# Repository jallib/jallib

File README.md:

# Welcome to **Jallib** 

This project holds a set of JAL libraries, compatible with the **JALV2** compiler. 
JAL is a high-level language for the Microchip 8-bits PIC microcontrollers of the
Baseline, Midrange, Enhanced Midrange and 18F series.

Lots of libraries exist, built by authors all over the world. The aim of this project is to:
 * Centralize these libraries.
 * Propose standards to write and share JAL code.

This avoids re-inventing the wheel and helps sharing code.

If you're looking for a specific library, welcome here! You may want to:
 * [Download](http://www.justanotherlanguage.org/downloads) one of our packages.
 * Browse our repository and retrieve sources. 
 * Browse the [Jal users site](http://www.justanotherlanguage.org) for introductions to JAL
in general and the use of several Jallib libraries in particular.

For a quick start on how to install Jallib, compile and run a jal program on your PIC have a look at [Installing and using Jallib](https://github.com/jallib/jallib/wiki/Installing-and-using-Jallib).

Also have a look at **UnixCompilingFromSvnHowto** wiki. It'll help you to use the whole repository.
 * jalapi is the jallib API documentation
 * have a look at our [jallib discussion group](https://groups.google.com/forum/#!forum/jallib),
where you can get some help on jallib libraries, jallib development or
* have a look at our [jallist discussion group](https://groups.google.com/forum/#!forum/jallist) where you can discuss coding issues with jal and PIC

The repository is organized in such a way that it is easy to find where you are looking for
(libraries, sample programs, device files, etc...). 
For a complete description, see the [Understanding The GitHub Structure](https://github.com/jallib/jallib/wiki/Understanding-The-GitHub-Structure) wiki.

If you plan to contribute, if you dare to put your head over the mowing field, welcome again! 
Go to the jallib discussion group and request to join us. 
For write access to the repository you'll need **GitHub account**. 
We'll be glad to send you a membership invitation! 
Once registered, you should have a look at our **JallibStyleGuide**. 
It will explain know some basic principles, rules, etc... 
which everyone must obey to provide efficient, understandable code. 
As a member, have a look at our [Jallib File Structure](https://github.com/jallib/jallib/wiki/Jallib-File-Structure). 
You'll be able to access our repository as an official committer!

Have fun !

The **Jallib team**.

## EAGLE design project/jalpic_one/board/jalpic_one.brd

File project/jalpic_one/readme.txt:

Information on the JALPIC One development board
===============================================

source
-------
Contains all source files of the controller PIC software
The Hex file for the controller PIC is also included in this directory.

examples
---------
Contains the two examples for showing the operation of the application PIC.
These examples are used in the documentation. This directory also contains
the jalpic_one.jal include file which has to be included by every program
that needs to run on the application PIC.
The Hex files of both example programs are also included in this directory.

board
-----
Contains all files used to create the board. These are:
-) Schematic diagram designed in Eagle 9.31
-) Board design designed in Eagle 9.31
-) PDF of the schematic diagram
-) PDF of the board design
-) PDF of the component layout
-) Screenshot of the board layout
-) Zipfile containing the Gerber files. This zipfile is used by the pcb
   manufacturer to manufacture the board.

doc
---
MS Word file of the user manual of the JALPIC One development board
PDF of the user manual of the JALPIC One development board

Tools
-----
This contains a zip file with 3 parts:
1) File jalpic_one.py. Python script to easy the programming of the JALPIC One development board.
2) Compiled version of jalpic_one.py for Windows 32-bit.
3) Compiled version of jalpic_one.py for Windows 64-bit.
See the manual on how to create a compiled version of this script.
When using the compiled version, Python does not have to be installed.

Notes
-----
After the zip file with the Gerber file was created, some small additions were made in the
silk screen of the board desing, e.g adding the text 'JALPIC One'. The board design itself
was not changed but note that when the zipfile is used to order a board, this text will not
be on it unless a new zipfile with Gerber file is created.

When using Python you need to have PySerial installed:
-) Python website: https://www.python.org/
-) Install PySerial: python -m pip install pyserial

A short video on how the board works can be found on: https://www.youtube.com/watch?v=lj-_5-6WYTY

Rob Jansen
2019-04-05

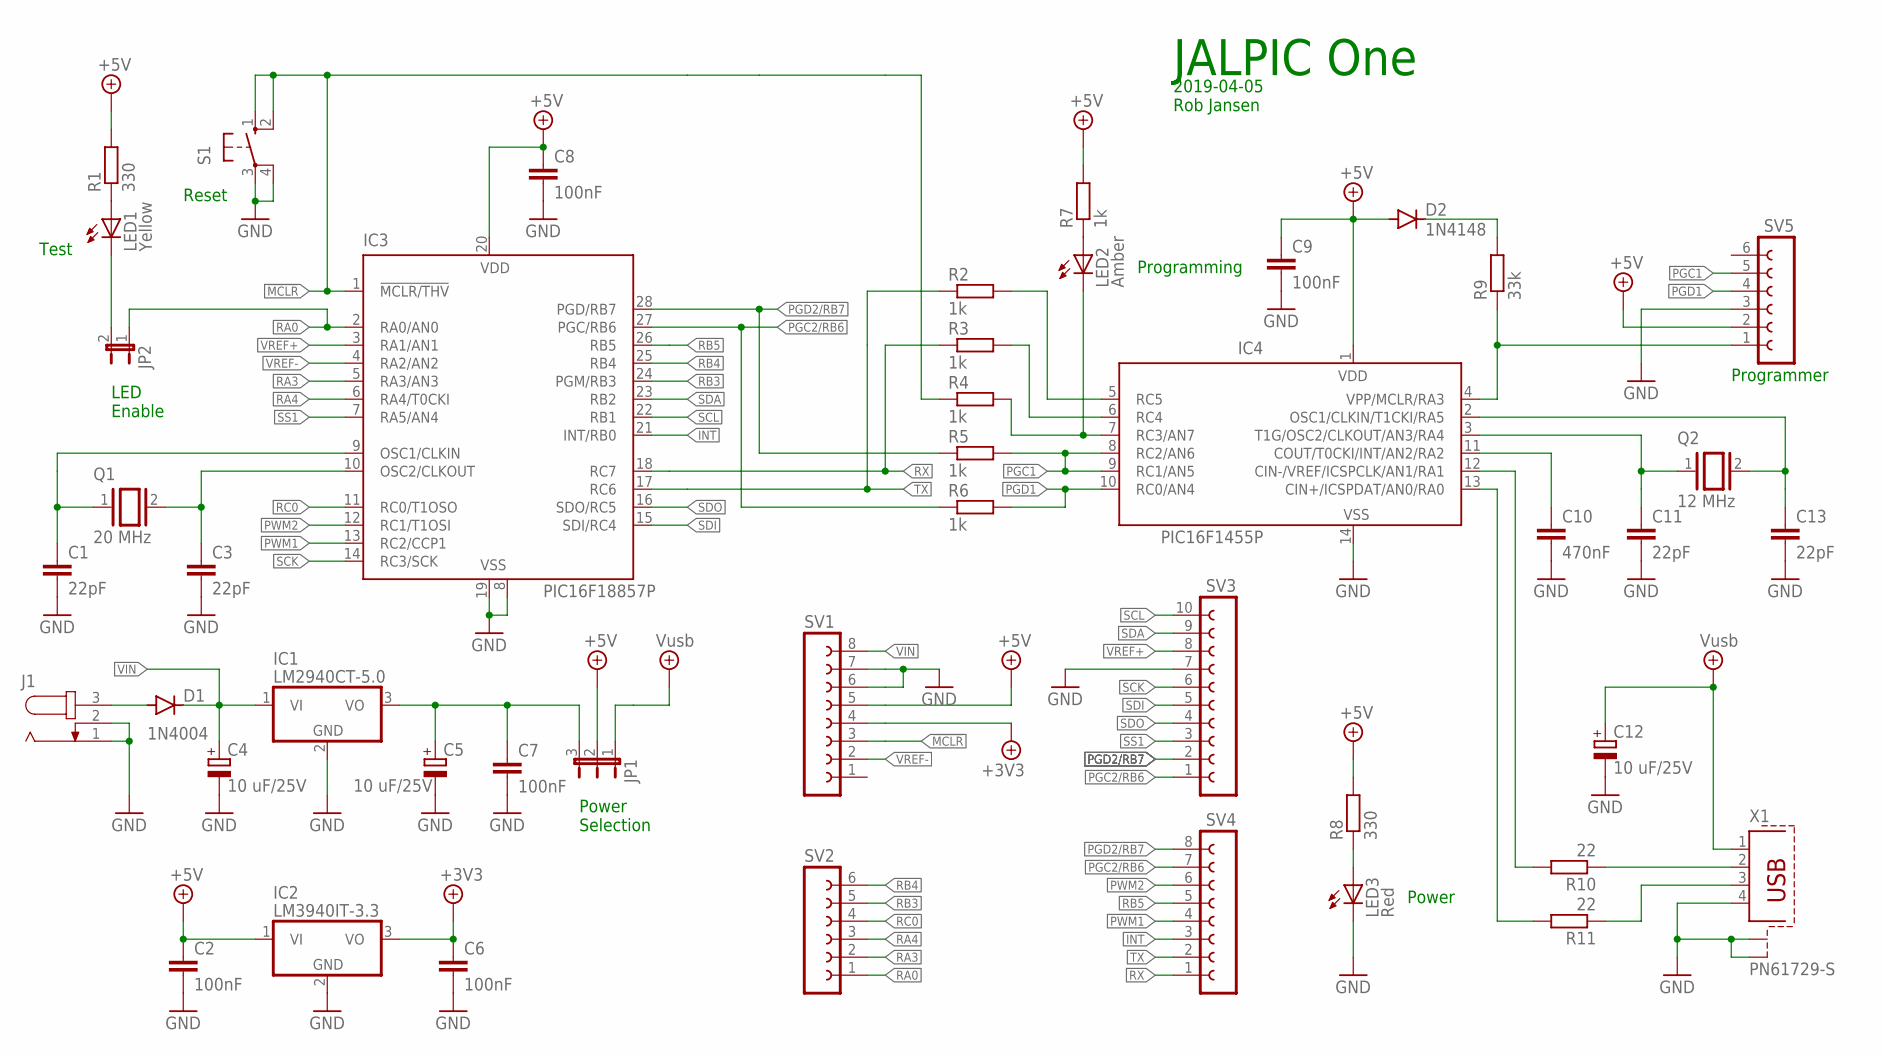
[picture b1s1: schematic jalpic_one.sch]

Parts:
C1, C3, C11, C13: 22pF; C050-024X044
C2, C6, C7, C8, C9: 100nF; C050-024X044
C4, C5, C12: 10 uF/25V; E2-5
C10: 470nF; C050-024X044
D1: 1N4004; DO35-7
D2: 1N4148; DO35-7
IC1: LM2940CT-5.0; TO220V
IC2: LM3940IT-3.3; TO220V
IC3: PIC16F18857P; DIL28-3
IC4: PIC16F1455P; DIL14
J1: JACK-PLUG0; SPC4077
JP1: JP2E; JP2
JP2: JP1E; JP1
LED1: Yellow; LED5MM
LED2: Amber; LED5MM
LED3: Red; LED5MM
Q1: 20 MHz; QS
Q2: 12 MHz; QS
R1, R8: 330; 0207/7
R2, R3, R4, R5, R6, R7: 1k; 0207/7
R9: 33k; 0207/7
R10, R11: 22; 0207/7
S1: 10-XX; B3F-10XX
SV1, SV4: FE08-1; FE08
SV2, SV5: FE06-1; FE06
SV3: FE10-1; FE10
X1: PN61729-S

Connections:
!MCLR: IC3.1 (!MCLR/THV), R4.1, S1.1 (S), S1.2 (S1), SV1.3
+4.1V: C6.1, IC2.3 (VO), SV1.4
+5V: C2.1, C8.1, C9.1, D2.A, IC2.1 (VI), IC3.20 (VDD), IC4.1 (VDD), JP1.2, R1.2, R7.2, R8.2, SV1.5, SV5.2
+9V: C12.+, JP1.1, X1.1
GND: C1.2, C2.2, C3.2, C4.-, C5.-, C6.2, C7.2, C8.2, C9.2, C10.2, C11.2, C12.-, C13.2, IC1.2 (GND), IC2.2 (GND), IC3.8 (VSS), IC3.19 (VSS), IC4.14 (VSS), J1.1, J1.2, LED3.K (C), S1.3, S1.4 (P1), SV1.6, SV1.7, SV3.7, SV5.3, X1.4, X1.S1, X1.S2
INT: IC3.21 (INT/RB0), SV4.3
unnamed: D1.A, J1.3
unnamed: IC4.4 (VPP/MCLR/RA3), R9.1, SV5.1
unnamed: JP2.2, LED1.K (C)
unnamed: C5.+, C7.1, IC1.3 (VO), JP1.3
unnamed: C10.1, IC4.11 (COUT/T0CKI/INT/AN2/RA2)
unnamed: LED1.A, R1.1
unnamed: LED3.A, R8.1
unnamed: IC4.7 (RC3/AN7), LED2.K (C), R4.2
unnamed: IC4.12 (CIN-/VREF/ICSPCLK/AN1/RA1), R10.2
unnamed: C11.1, IC4.3 (T1G/OSC2/CLKOUT/AN3/RA4), Q2.1
unnamed: C13.1, IC4.2 (OSC1/CLKIN/T1CKI/RA5), Q2.2
unnamed: C3.1, IC3.10 (OSC2/CLKOUT), Q1.2
unnamed: IC4.6 (RC4), R3.2
unnamed: IC4.5 (RC5), R2.2
unnamed: IC4.13 (CIN+/ICSPDAT/AN0/RA0), R11.2
unnamed: C1.1, IC3.9 (OSC1/CLKIN), Q1.1
unnamed: LED2.A, R7.1
unnamed: R10.1, X1.2
unnamed: R11.1, X1.3
unnamed: D2.C, R9.2
PGC1: IC4.8 (RC2/AN6), IC4.9 (RC1/AN5), R5.2, SV5.5
PGC2/RB6: IC3.27 (PGC/RB6), R6.1, SV3.1, SV4.7
PGD1: IC4.10 (RC0/AN4), R6.2, SV5.4
PGD2/RB7: IC3.28 (PGD/RB7), R5.1, SV3.2, SV4.8
PWM1: IC3.13 (RC2/CCP1), SV4.4
PWM2: IC3.12 (RC1/T1OSI), SV4.6
RA0: IC3.2 (RA0/AN0), JP2.1, SV2.1
RA3: IC3.5 (RA3/AN3), SV2.2
RA4: IC3.6 (RA4/T0CKI), SV2.3
RB3: IC3.24 (PGM/RB3), SV2.5
RB4: IC3.25 (RB4), SV2.6
RB5: IC3.26 (RB5), SV4.5
RC0: IC3.11 (RC0/T1OSO), SV2.4
RX: IC3.18 (RC7), R3.1, SV4.1
SCK: IC3.14 (RC3/SCK), SV3.6
SCL: IC3.22 (RB1), SV3.10
SDA: IC3.23 (RB2), SV3.9
SDI: IC3.15 (SDI/RC4), SV3.5
SDO: IC3.16 (SDO/RC5), SV3.4
SS1: IC3.7 (RA5/AN4), SV3.3
TX: IC3.17 (RC6), R2.1, SV4.2
VIN: C4.+, D1.C, IC1.1 (VI), SV1.8
VREF+: IC3.3 (RA1/AN1), SV3.8
VREF-: IC3.4 (RA2/AN2), SV1.2

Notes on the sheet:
JALPIC One
2019-04-05 Rob Jansen
Power
Power Selection
Programming
Reset
Programmer
LED Enable
Test

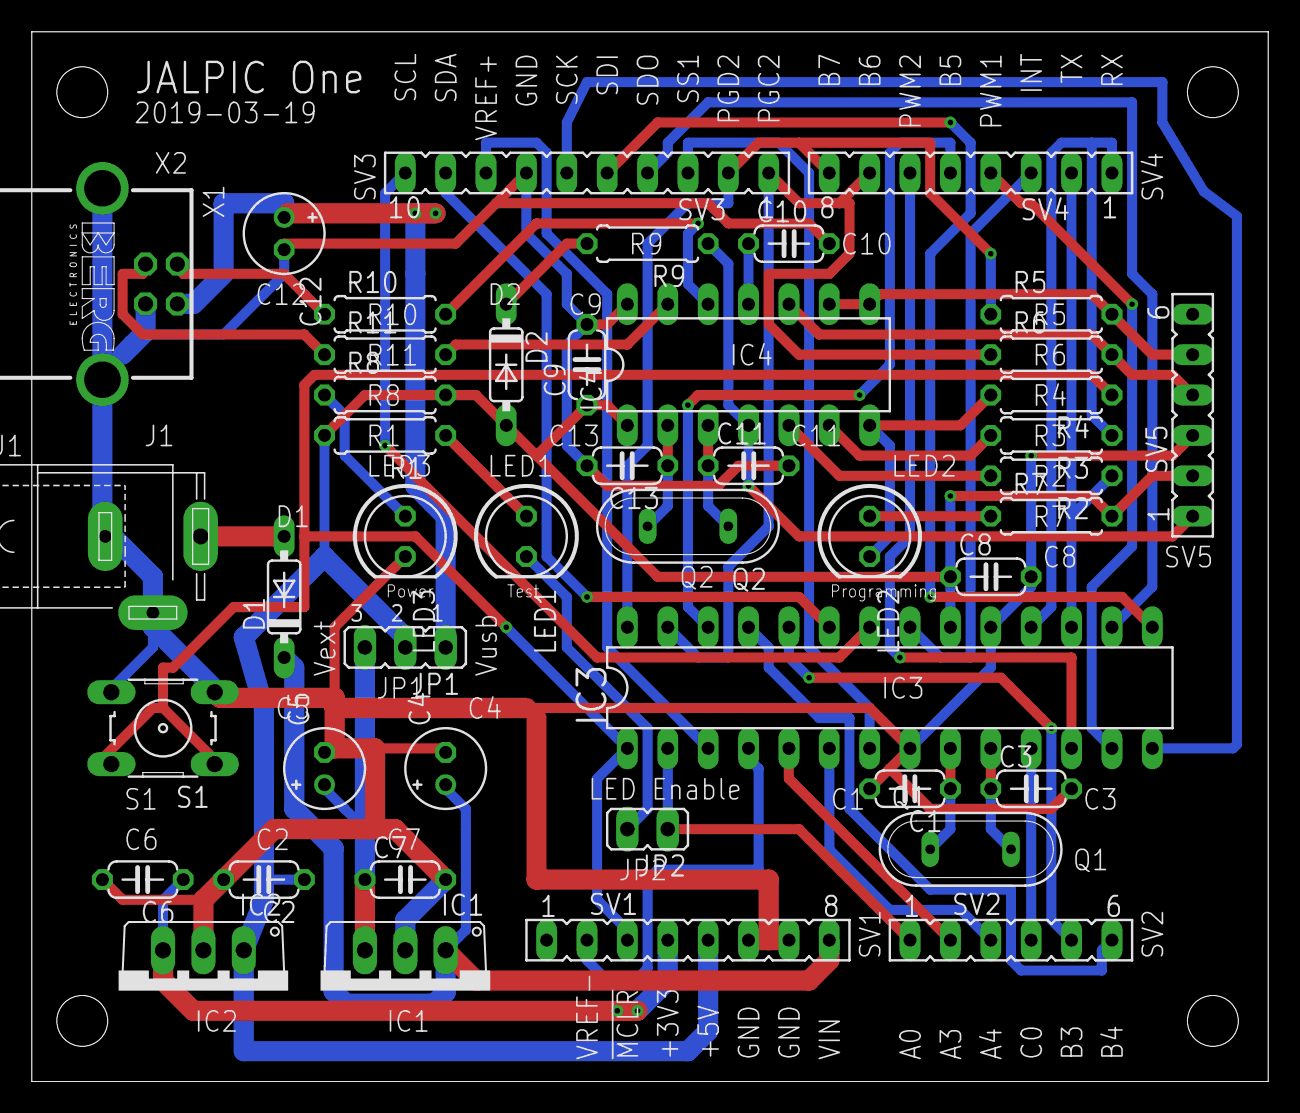
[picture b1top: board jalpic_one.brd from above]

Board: 2 copper layers, 77.8 x 66.0 mm, 45 parts (0 on the bottom side), 50 nets.

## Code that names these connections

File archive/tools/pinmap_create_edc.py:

#!/usr/bin/python

"""
   pinmap_create.py - create new pinmap.py from MPLAB-X
   This script is part of a sub-project using MPLAB-X info for Jallib,
   in particular the device files, but also for some other libraries.
   This script uses the .edc files created by the pic2edc script.
   The Pin section of these files contains the pin aliases.
   Some manipulations are performed, for example:
    - skip pins which are not accessible from the program like Vpp, Vdd
    - skip non-aliases of a pin, like IOC, INT
    - correct apparent errors or omissions of MPLAB-X
    - determine the base name of a pin and specify it as first in list
   When pins are not in .edc file or known to be incorrect
   the entry in the old pinmap file will be copied (when present).
   Same when the .edc file does not contain a Pin section at all,
   otherwise the pinmap will not contain an entry for this PIC and
   must be created manually from the datasheet.
   This script handles issues with MPLAB-X (version see below).
   for other MPLAB-X versions it will probably have to be adapted!
"""

import os
import sys
import fnmatch
import re
from xml.dom.minidom import parse, Node

mplabxversion = "205"                                       # latest version of MPLAB-X

edcdir    = "k:/jal/edc2jal/edc_" + mplabxversion           # dir with .edc files
pinmapnew = "pinmapnew.py"                                  # output

portpin = re.compile(r"^R[A-L]{1}[0-7]{1}\Z")               # Rx0..7 (x in range A..L)
gpiopin = re.compile(r"^GP[0-5]{1}\Z")                      # GP0..5

dir = fnmatch.filter(os.listdir(edcdir), "*.edc")           # get list of .edc files
if len(dir) == 0:
   print "No .edc files found in directory", edcdir
   sys.exit(1)

print "Building new pinmap from .edc files in", edcdir, "for (max)", len(dir), "PICs"

try:
   fp = open(pinmapnew, "w")
except IOError:
   print "Could not create output file", pinmapnew
   sys.exit(1)


def list_pic(_pic, _alias):
# list all pins and their aliases of a single _pic in dictionary _alias
   header = '   "' + _pic + '": {'                          # start of pinmap this PIC
   fp.write(header)
   pinlist_sorted = list(_alias.keys())
   pinlist_sorted.sort()
   for i in range(len(pinlist_sorted) - 1):                 # all but last
      pin = pinlist_sorted[i]
      fp.write('"' + pin + '" : ["' + '", "'.join(_alias[pin]) + '"],\n' + " "*len(header))
   pin = pinlist_sorted[-1]
   fp.write('"' + pin + '" : ["' + '", "'.join(_alias[pin]) + '"]\n' + " "*len(header))
   fp.write("},\n")                                         # end of pinmap this PIC


from pinmap import pinmap                                   # current ('old') pinmap

dir.sort()                                                  # alphanumeric sequence
piccount = 0
fp.write("pinmap = {\n")                                  # pinmap header

for filename in dir:
   picname = os.path.splitext(filename)[0][0:].upper()      # determine PIC from filename
   print picname

   if (picname in ("16LF1713", "16F1716", "16LF1716")):
      filename = "16f1713.edc"
      print "  Pinmap derived from 16f1713"

   filepath = os.path.join(edcdir,filename)                 # pathspec
   dom = parse(filepath)                                    # load .edc file

   pinnumber = 0
   pinlist = {}                                             # new dictionary
   for pin in dom.getElementsByTagName("edc:Pin"):          # select pin nodes
      pinnumber = pinnumber + 1                             # calculated next pin, maybe
      for pinc in pin.childNodes:                           #   corrected by comment node
         if pinc.nodeType == pinc.COMMENT_NODE:
            wlist = pinc.nodeValue.split()
            if wlist[0].isdigit() == True:
               pinnumber = int(wlist[0])
            elif wlist[1].isdigit() == True:
               pinnumber = int(wlist[1])
      aliaslist = []                                        # new aliaslist this pin
      for vpin in pin.getElementsByTagName("edc:VirtualPin"):
         alias = vpin.getAttribute("edc:name").upper().strip("_")
         if alias not in ("INT", "IOC"):                    # only 'real' alias names
            if alias.startswith("RB")  & picname.startswith("12"):   # Jallib requirement
               aliaslist.append("RA" + alias[-1])           # RBx -> RAx
               aliaslist.append("GP" + alias[-1])           # add GPx
               print "  Renamed pin", alias, "to RA" + alias[-1]
            elif alias in("RB1AN10", "RC7AN9"):             # MPLAB-X errors
               aliaslist.append(alias[0:3])
               aliaslist.append(alias[3:])
               print "  Splitted alias", alias, "into", alias[0:3], "and", alias[3:], "for pin", pinnumber
            elif alias == "DAC1VREF+N":                     # MPLAB-X error
               aliaslist.append("DAC1VREF+")
               print "  Replaced", alias, "by DAC1VREF+ for pin", pinnumber
            elif alias == "NMCLR":
               aliaslist.append("MCLR")
               print "  Replaced", alias, "by MCLR for pin", pinnumber
            elif ( (picname in ("16F1707", "16LF1707")) &
                   (alias == "AN9") & (pinnumber == 8) ):
               aliaslist.append("AN8")
               print "  Replaced alias", alias, "by AN8 for pin", pinnumber
            elif ( (picname in ("18F2439", "18F2539", "18F4439", "18F4539")) &
                   (alias.startswith("PWM")) ):
               aliaslist.append(alias)
               if alias[-1] == "1":
                  aliaslist.append("RC2")                   # MPLAB-X omission
                  print "  Added RC2 to pin", pinnumber
               else:
                  aliaslist.append("RC1")
                  print "  Added RC1 to pin", pinnumber
            else:
               aliaslist.append(alias)                      # normal alias!

      if (picname in ("18F2331", "18F2431")) & (pinnumber == 26):
         aliaslist = ["RE3"] + aliaslist                    # prepend missing pin name
         print "  Added RE3 to pin", pinnumber
      elif (picname in ("18F4220", "18F4320")) & (pinnumber == 36):  # MPLAB-X omission
         aliaslist = pinmap[picname].get("RB3", ["RB3"])    # copy from old pinmap if present
         print "  Aliaslist of pin", pinnumber, "copied from old pinmap"
      elif (picname in ("18F86J11", "18F86J16", "18F87J11"))  & (pinnumber == 55):
         aliaslist = pinmap[picname].get("RB3", ["RB3"])    # copy from old pinmap if present
         print "  Aliaslist of pin", pinnumber, "copied from old pinmap"

      portbit = None
      for alias in aliaslist:
         if re.match(portpin,alias):                        # check for Rxy
            portbit = alias
            if portbit != aliaslist[0]:                     # not first in list
               aliaslist.remove(portbit)
               aliaslist = [portbit] + aliaslist            # shift to front
            break
         elif re.match(gpiopin,alias):                      # check gor GPx
            portbit = "RA" + alias[-1]                      # note: RAx not in aliaslist!
            break
      if portbit != None:                                   # found Rxy or GPx
         if portbit in pinlist:
            print "  Duplicate pin specification:", portbit, "pin", pinnumber, "skipped"
         else:
            pinlist[portbit] = aliaslist                    # add aliaslist this pin


   if picname in ("16F1704", "16LF1704"):
      for pin in ("RB4", "RB5", "RB6", "RB7", "RC6", "RC7"):
         if pinlist.get(pin) == None:                       # MPLAB-X omission
            if pinmap[picname].get(pin) != None:            # pin present in old pinmap
               pinlist[pin] = pinmap[picname].get(pin)      # take it from old pinmap
               print "  Copied missing alias list of pin", pin, "from old pinmap"
            else:
               pinlist[pin] = [pin]                         # insert dummy
               print "  Inserted dummy alias list for missing pin", pin

   if len(pinlist) > 0:
      list_pic(picname, pinlist)                            # list pinmap this pic
      piccount += 1
   elif pinmap.get(picname) != None:                        # present in old list
      list_pic(picname, pinmap[picname])                    # copy old mapping
      piccount += 1
      print "  Pinlist missing in .edc file, entry copied from current pinmap"
   else:
      print "  Pinlist missing, add it manually!"

fp.write("  }\n")                                           # end of pinmap
fp.close()

print "Generated pinmap", pinmapnew, "for", piccount, "PICs"
print "Compare new with current, when OK copy", pinmapnew, "to pinmap.py"

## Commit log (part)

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2021-01-03 Added new blink samples using internal oscillator.
2021-01-03 Added missing blink samples.
2021-02-09 Update pps.jal
    Alias added to support newer PICs. Work done by Oliver "Kiste" Seitz.
2021-02-11 Update jalv2.pdf
    Added a limitations section, like MVECEN, XINST, etc.
2021-03-07 Added new devices with blink samples.
    18f27q83 and 18f57q83 but not yet part of release.
2021-03-20 Update 16f15325_bt_hc06.jal
    Small bugfix,
2021-04-03 Update bt_hc06.jal
    Small code cleanup.
2021-04-05 Update jalv2.pdf
    Added CONST example
2021-04-17 Added Visual Studio Code tasks.json file
    Links to this file from a Wiki page.
2021-06-25 Added alias and 2 ms delay for PLL for 18f27j53
2021-07-10 Update TORELEASE
    Removed adc_clock.jal --> to casualties
2021-07-29 Fixed missing input pins RC4 and RC5 for 18(L)F PICs with USB
2021-09-10 Update sd_card.jal
    Fixed sd card write error in sd_data_byte'put
2021-09-25 Fixing compiler issues#23 and issue#24
    Part of jalv25r5 build of september 23, 2021.
2021-10-02 Update of DS3231 RTC library with alarm functionality.
    Also changed sample file from 16f1823 to 16f1825.
2021-10-05 Update TORELEASE
    Added some blink samples that should be in the release.
2021-10-07 Update TORELEASE
    Added 560 new blink sample files to the release. Mostly intosc sample files.
2021-10-10 Update TORELEASE
    Removed sample file preventing bee-package to be created.
2021-11-13 Update glcd_ssd1306.jal
    Small fix as to be able to select another IIC bus speed.
2021-11-20 Update LICENSE.zlib
    Added Matt & Rob J :-)
2021-12-05 Moved mouse sample
2021-12-09 Update CHANGELOG
2021-12-10 Uncomment function sd_error'get()
2021-12-19 Add files via upload
    Reverted synchronous version of WS2812b library to 'external polarity inverter required'.
2021-12-19 Removed files from root directory
2021-12-27 usb msd command inquiry response fix
2022-01-08 Wrong sample was removed. Adding back 18f67j50_usb_hid_mouse.jal
2022-02-02 MPLABX V6.00 Update
2022-02-05 Improved documentation of library and sample for DS3231
2022-02-19 Update of Tutorial Book
    First update. Work not yet completed. Fixed broken links and removed references to SVN and Google fpr download, replaced this by the Jallib website.
    Also removed the errors when generating the tutorial books.
2022-02-20 Update of Tutorial Book
    All tutorials are up to date and all broken links have been updated or removed.
2022-02-27 Added Large Array tutorial to Tutorial Book
2022-03-06 Small fixes for Tutorial Book. Released version 0.5
2022-03-19 Added how to make a tutorial to the Tutorial Book
    And fixed issue in the tutorial about the visual studio plug-in.
2022-04-02 Moved compiler documentation to compiler repository.
2022-05-22 Update jallib.py
    Removed commented out $Revision.
2022-06-05 Added library for PCA9685 including sample files.
    16 channel, 12-bit PWM IIC LED controller.
    (but can also be used for servo control)
2022-06-27 Update of USB in Tutorial Book
    Moved schematic diagram from USB part 1 to part 2 and added 'Ohm' to resistor values < 1k.
2022-08-06 Added temperature feature to ds3231 library.
    Including update of sample to show the temperature.
2022-09-10 Added library and sample files for ili9341 graphics color display
    Including sample bitmap files in the project folder ili9341.
    Some fixes where needed for glcd_common.jal and sd_card.jal to support this library with these sample files.
2022-09-17 Moved glcd_touch_stm032qvt and glcd_touch_ad7843 to casualties
2022-09-22 Added variable display size to glcd_common.
    Also update of glcd_common to deal with bigger fonts (fonts and update of glcd_font will follow later).
    Small ili9341 library updated including sample file since variable display size moved to glcd_common.
2022-09-24 Added two extra large arrays
    large_array_5.jal and large_array_6.jal
2022-10-02 Added mirroring to ili9341 and ads7843 libraries
    Some displays are configured differently and require mirroring of the default settings.
2022-10-05 Small fixe of ili9341 library.
    Also small update of sample files to work with the internal oscillator.
2022-10-09 Bugfix in ili9341.jal library
    Removed frog image and added new images including some images in JAL format.
2022-10-22 Fixed SPI pinning in sample files.
2022-11-12 Moved code from spi_master_hw.jal to spi_host_hw.jal due to terminology concerns.
2022-11-14 Removed include spi_common
    Already included by spi_host.
2022-11-27 Update of pic_data_eeprom.jal
    Included a new sample file for the pic16f19176.
2022-12-15 Added serial speed converter with 16f18015
2022-12-16 Small update of tm1637 library
    Renamed one sample file with keyboard and added a sample file for 4 displays without a keyboard.
2022-12-24 Fix of about 90 blink intosc samples.
    4 MHz was not set for those samples.
    All blink sample files where uploaded since compiler version was also updated.
2023-01-12 Added new device files and new blink samples.
    For 16f18056 and 16f18076.
2023-01-29 Compiler rebuild.
    Fixing issue when running the Linux compiler on some computers.
2023-02-15 Update VS Code tasks.json
    Fixing problem building a program from Visual Studio Code.
2023-04-08 Update CHANGELOG
    Added update of jalv2 compiler documentation.
2023-04-21 Update of DS3231 Library and sample file.
    Added functions to read back the set alarm 1 and alarm 2 time in binary or bcd format.
2023-04-28 Update rtc_ds3231.jal
    Fix to prevent reset of RTC date and time after power up (even with battery).
2023-05-19 JAL compiler update version jalv25r8
    Fixed compiler issues #28, #30 and #31.
2023-05-21 Create jalbuild.yml
    Perform a JAL build using GitHub Actions
2023-05-22 Update CHANGELOG
    To trigger a new build.
2023-05-28 Delete jalv2-osx
    Had to remove it before replacing it.
2023-06-01 Update README.txt
    Small textual change (and trigger the webhook)
2023-06-14 Update of stopwatch and stopwatch2 library
    To support newer PIC. Added two new stopwatch sample files for pic16f15325.
2023-07-30 Fixing Jallib Tutorial for new Dita version
2023-08-01 Update Makefile
2023-08-26 Update TORELEASE
    Fixed typo.
2023-09-03 Corrected name of init procedures.
2023-09-23 Added library and sample file for decoding the DCF77 signal.
    Also renamed one sample file for gps_neo_6m for consistency.
2023-10-01 Added sample for remote control decoders.
    And renamed some.
2023-10-27 Added new device files and blink samples.
    For 16f17156 and 16f17176
2023-12-11 Small update of Tutorial Book
2024-01-20 Small textual updates
2024-01-27 Added new devices and new sample files.
    For 16f18154, 16f18155, 16f18174, 16f18175.
2024-03-02 MPLABX V6.20 update
    Adding new - not yet released - device files and blink sample files.
2024-04-12 Update CHANGELOG
    Release of Jallib 1.9.0.
2024-04-13 Fixed typo in filename.
2024-04-14 Added mcp23x08 8-bit i/o expander with serial interface.
    mcp23s08 with spi interface
    mcp23008 with i2c interface
    Also moved shift_register library to io directory.
2024-04-20 Multiprocessor function added to python scripts
    Update by RobH.
2024-05-04 Added new device files and blink sample files
    For 16f13113, 16f13114, 16f13115, 16f13123, 16f13124, 16f13125, 16f13143, 16f13144, 16f13145.
    Also updated ZLIB license copyright year..
2024-05-18 Removed reset from init and moved library to pressure directory.
2024-08-11 Update of Jallib Tutorial Book
    Changed USB tutorial schematic and sample program so that the PIC programmer can stay connected.
2024-08-15 Added new device files and blink samples.
    For 18f24q71, 18f25q71, 18f44q71, 18f45q71, 18f54q71 and 18f55q71.
2024-08-23 Added jallib_tutorial_book
2024-11-23 Small update of library.
    Added compiler optimization and moved SPI definition from library to sample program.
2024-12-25 Update print.jal
    Made print string inline due to compiler issue #33
2024-12-27 Fixing assert.
2024-12-28 Removed assert.
2025-01-04 Update of library nrf24l01.
    Moved SPI initialization to sample program as to enable the use of SPI hardware 2. This is a breaking change for this library. Sample files adapted.
2025-01-04 Update jalv2-osx
2025-02-07 Fixed device files for 16f1713 and 16f1716
    pic2jall script also updated.
2025-03-02 updated release instructions
2025-03-07 Update CHANGELOG
    Added update of MPLABX_v6.25
2025-03-08 Added new device files and samples
    For 18f04q20, 18f05q20, 18f14q20, 18f15q20
2025-03-15 Update of pic2jal.py
    Generating a sorted list of PICs for chipdef_jallib.jal
2025-03-22 Added missing device files and sample files.
    Did an update of all device files and sample files to be sure that all are in.
2025-07-18 Added library vl53l0x time-of-flight ranging sensor.
    Including two sample files for continuous mode and single mode.
    Also fixed Python script jallib3.py solving warnings about escape sequences.
2025-07-18 Update jallib3.py
    Added errors='ignore' when opening files to solve utf-8 validation problem in some JAL libraries.
2025-08-10 Update to support newer PICs
    Supporting e.g. 16f13115
2025-09-03 adding check package script with multi-processing compile
2025-09-06 Small fix and sample update
    Included example of using alert in sample program.
2025-09-08 Updated CHANGELOG and TORELEASE for sd card crc updates
2025-09-14 added if defined statement, for backwards compatibility.
2025-09-20 Fixed serial port requirement in sd_card.jal, reverted sd_init and get sectors procedures
2025-09-21 Removed print statements from the sd_card library used during testing.
2025-09-22 Updated storage drivers library for backwards compatibility. sector buffer was changed from 2x 256 byte arrays to one 512 byte large array
2025-09-25 Update of ssd1306 library
    Supports writing bigger fonts. Sample files updated. Also moving interface to the sample files instead of the library.
2025-10-19 Test for moving blink samples
    The blink sample are currently also available in the sample folder.
2025-10-19 Added missing intosc blink samples
2025-10-24 Revert "Changes for blink in separate folder"
    This reverts commit 12ab0001d5806f5f02afefc530503269f016d341.
2025-10-26 removed dupe blink samples (were moved to sample/blink)
2025-10-28 Update of TORELEASE
    Fixed script torelease.py using new blink sample structure.
2025-11-01 Python scripts using environment variables.
    Hard paths to directories where removed. For all changed Python scripts a bash file and bat file was added to set the environment variables.
2025-11-03 File constants_jallib.py retrieved from jallib/include
    The file constants_jallib.py was retrieved from the current working directory (thus from which this script was called). With this changed it will be retrieved from the jallib/include directory.
2025-12-21 Update of compiler doc
2025-12-28 Update convert_bmp_to_jal_array.py
    Added option to create an array using Big Endian instead of Little Endian.
2025-12-29 Update of stopwatch libraries
    For newer PICs, added sample files for 18f15q40. Also added sample for memory pointer and included jal logo in sample file 16f18867_glcd_ili9341.
2026-01-16 Update of glcd_ks0108.jal library
    Supports lager horizontal fonts next to vertical fonts. Included an extra sample program to demonstrate this.
2026-01-21 Update tutorial_style_guide.xml
    Added header for guide for procedures and functions.
2026-01-23 Jallib Tutorial Book Page Break Support
2026-01-28 Added a simple ICSP schematic image to tutorials.
2026-01-30 Small cleanup
    And changed license to ZLIB.
2026-02-05 Updated Seven Segment Multiplexer library internal/external routine names fixing underscore. Improved routine descriptions.
2026-02-05 Makefile changes to align with release, added bee-win, updated release instructions updated win installer to match the new makefile. changed name dev to alpha
2026-02-28 MPLABX V6.30 update
    Fixed missing DEBUG in device files.
2026-03-16 Added serial hardware samples for 12f1840
2026-04-04 Added sample 12f1840_glcd_ssd1306_number_font.jal
2026-04-24 Added bmp images to the project file.
    Image used in the SD card sample files for the st7735 and st7789.
